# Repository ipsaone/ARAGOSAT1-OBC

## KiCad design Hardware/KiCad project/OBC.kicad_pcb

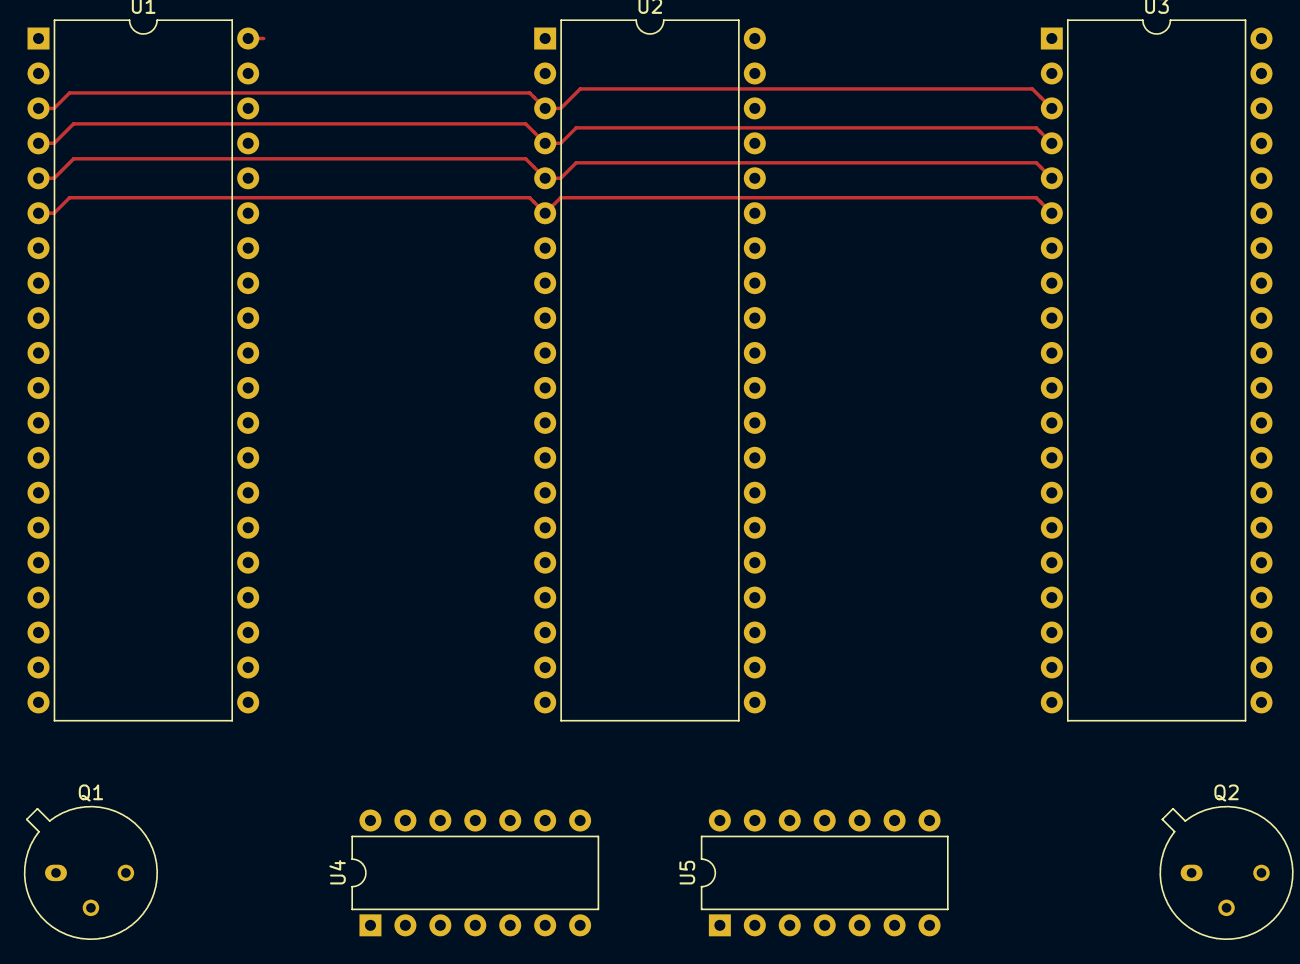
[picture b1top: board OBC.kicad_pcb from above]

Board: 2 copper layers, 7 parts (0 on the bottom side), 15 nets.

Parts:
Q1, Q2: 2N2219; TO-39-3
U1, U2, U3: ATmega32-16PU; DIP-40_W15.24mm
U4, U5: 7408; DIP-14_W7.62mm

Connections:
+5V: U1.10, U1.30, U2.10, U2.30, U3.10, U3.30
/CPU_0: U1.39, U4.12, U5.5
/CPU_1: U2.39, U4.13, U5.1
/CPU_2: U3.39, U5.2, U5.4
/PWR_0: U1.40, U4.1, U4.10
/PWR_1: U2.40, U4.2, U4.4
/PWR_2: U3.40, U4.5, U4.9
/PWR_CONSENSUS: Q1.3, Q2.3
GND: U1.11, U1.31, U2.11, U2.31, U3.11, U3.31
Gnd: U4.7, U5.7
Vcc: U4.14, U5.14
WD_MISO: U1.5, U2.5, U3.5
WD_MOSI: U1.4, U2.4, U3.4
WD_SCK: U1.6, U2.6, U3.6
WD_SS: U1.3, U2.3, U3.3

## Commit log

2018-12-06 Created folders and their READMEs
2018-12-09 first watchdog schema
2018-12-13 Updated majority voting circuits
2019-06-11 First prototype migrated to Altium Designer
2019-06-11 Fix some compilation errors
2019-06-11 Memory/Flash pos update
2019-06-11 Fix fatal compilation errors
2019-06-11 Clean-up
2020-05-07 Refactor and add emulator
2020-05-07 Add readme
2020-05-07 create Vagrantfile
2020-05-07 Add configure file, vm bootup fix and raspbian download URL
